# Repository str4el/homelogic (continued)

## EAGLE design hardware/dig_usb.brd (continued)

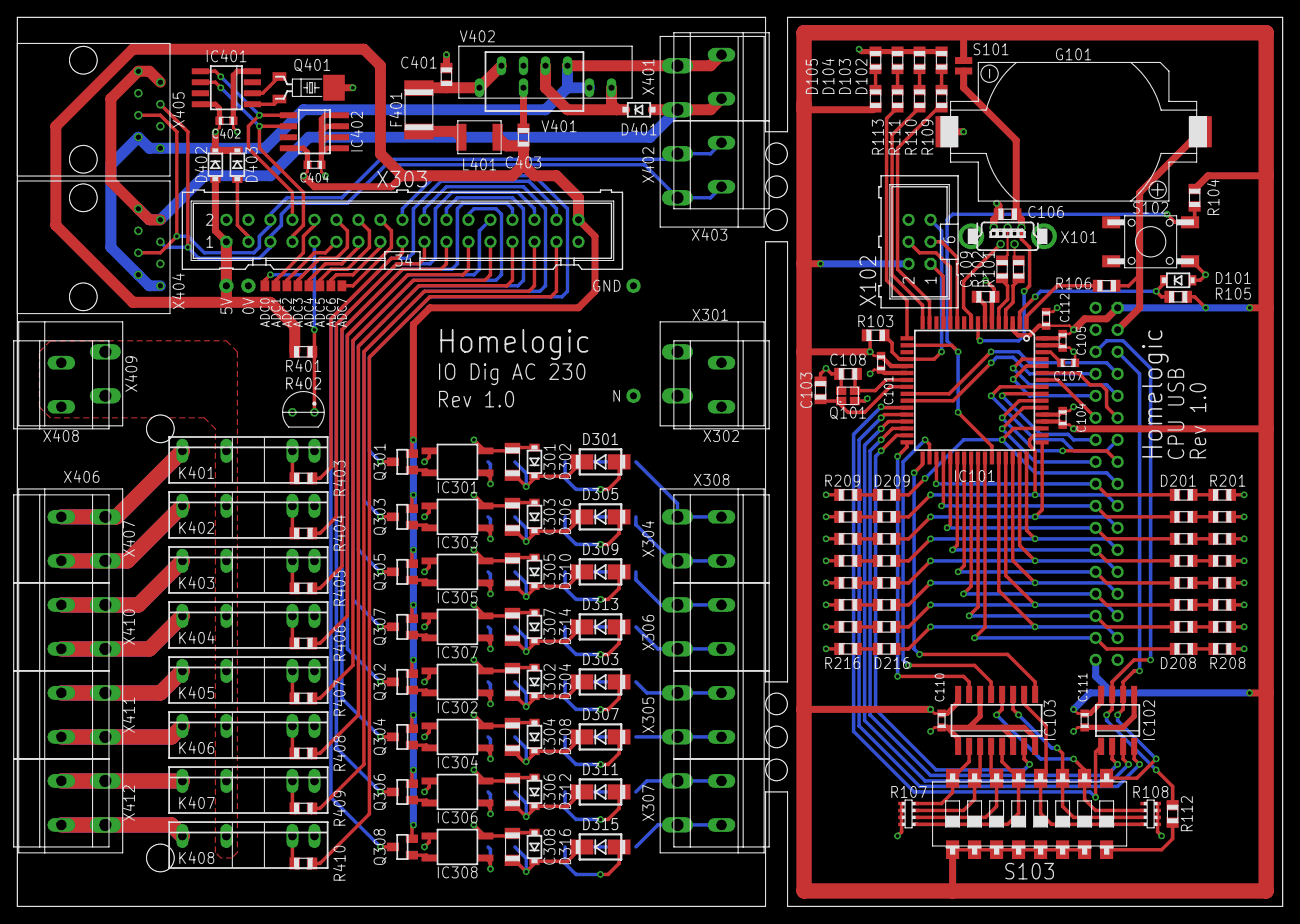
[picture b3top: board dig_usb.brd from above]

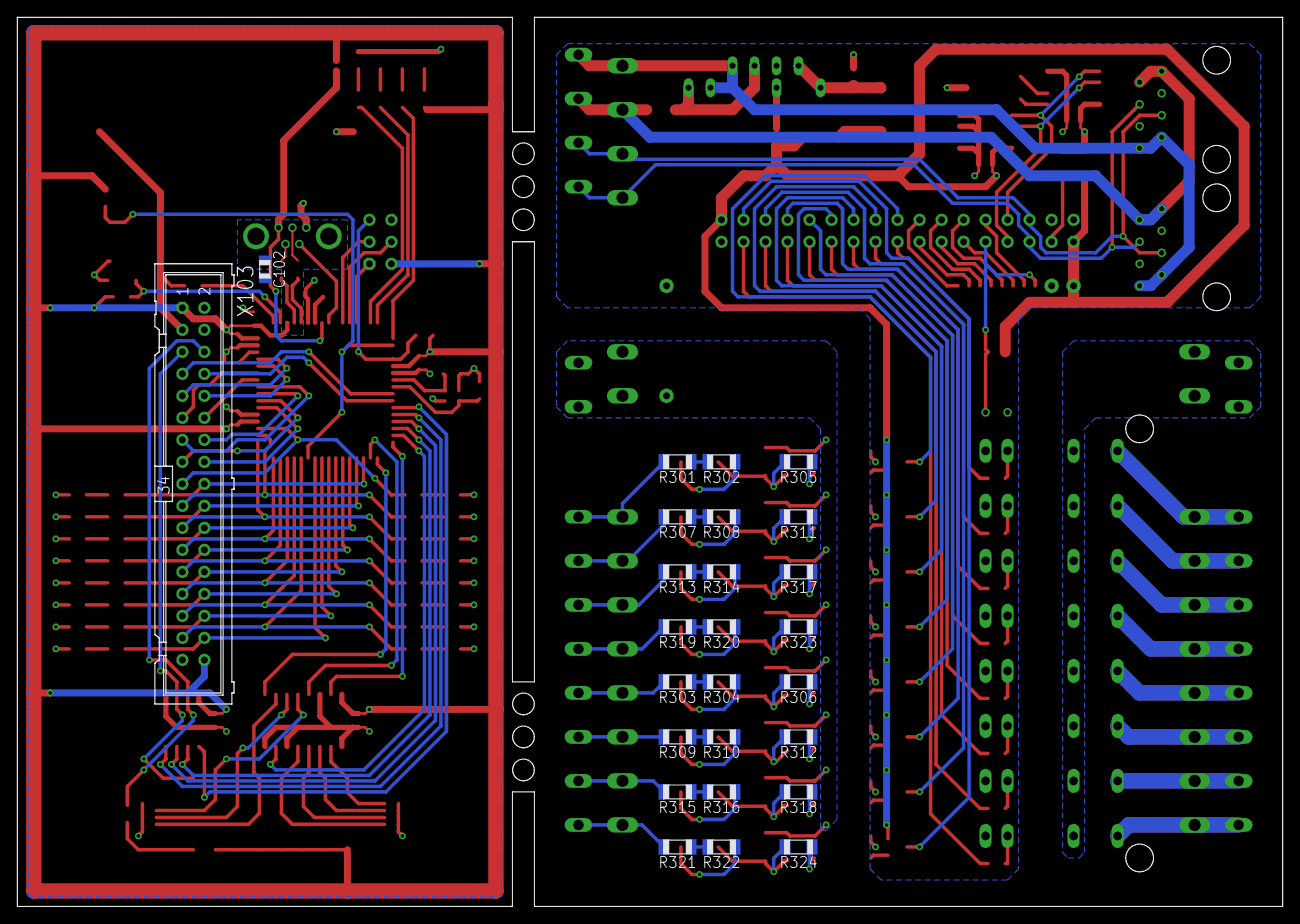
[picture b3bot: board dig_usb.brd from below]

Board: 2 copper layers, 146.1 x 102.6 mm, 201 parts (26 on the bottom side), 191 nets.

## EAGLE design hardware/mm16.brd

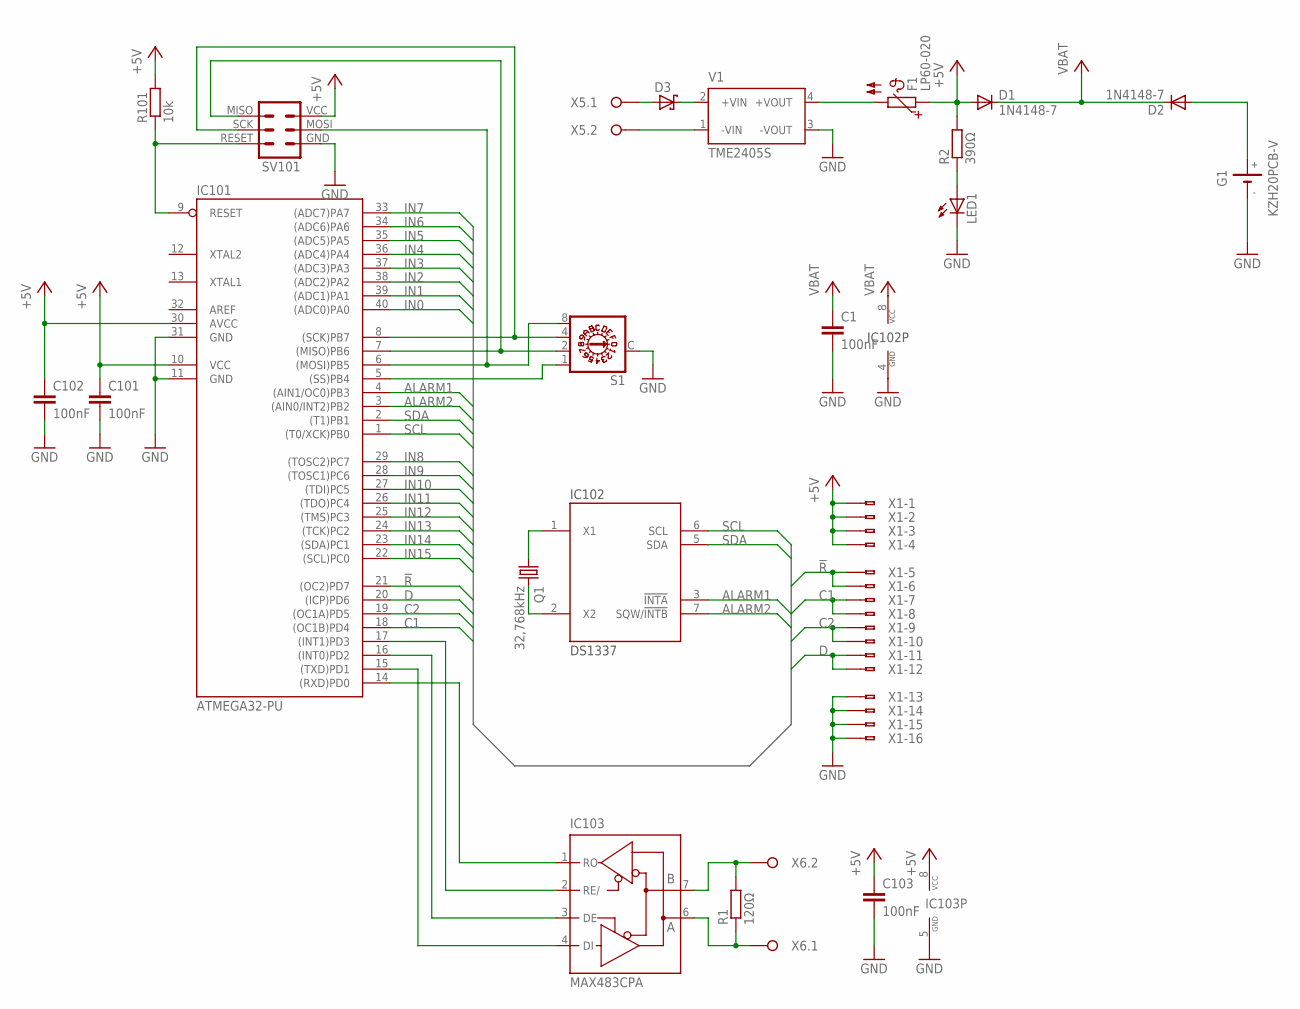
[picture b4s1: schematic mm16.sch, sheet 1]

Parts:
C1, C101, C102, C103: 100nF; C025-025X050
D1, D2: 1N4148-7; DO35-7@1
D3: SCHOTTKY-DIODEDO35-7; DO35-7
F1: LP60-020
G1: KZH20PCB-V
IC101: ATMEGA32-PU; DIL40
IC102: DS1337; DIL08
IC103: MAX483CPA; DIL08
LED1: LED3MM
Q1: 32,768kHz; TC38H
R1: 120Ω; 0204V
R2: 390Ω; 0204V
R101: 10k; 0204V
S1: P103
SV101: AVR_ISP6; ML6
V1: TME2405S; TME-24V; MPN TME 2405S
X1: WS16V
X5, X6: WAGO_236-402

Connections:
!R: IC101.21 ((OC2)PD7), X1.5, X1.6
+5V: C101.1, C102.1, C103.1, D1.A, F1.P$1 (1), IC101.10 (VCC), IC101.30 (AVCC), IC103.8 (VCC), R2.2, R101.2, SV101.VCC, X1.1, X1.2, X1.3, X1.4
ALARM1: IC101.4 ((AIN1/OC0)PB3), IC102.3 (!INTA)
ALARM2: IC101.3 ((AIN0/INT2)PB2), IC102.7 (SQW/!INTB)
C1: IC101.18 ((OC1B)PD4), X1.7, X1.8
C2: IC101.19 ((OC1A)PD5), X1.9, X1.10
D: IC101.20 ((ICP)PD6), X1.11, X1.12
GND: C1.2, C101.2, C102.2, C103.2, G1.-, IC101.11 (GND), IC101.31 (GND), IC102.4 (GND), IC103.5 (GND), LED1.K (C), S1.C, SV101.GND, V1.3 (-VOUT), X1.13, X1.14, X1.15, X1.16; also elsewhere on the board
IN0: IC101.40 ((ADC0)PA0); also elsewhere on the board
IN1: IC101.39 ((ADC1)PA1); also elsewhere on the board
IN2: IC101.38 ((ADC2)PA2); also elsewhere on the board
IN3: IC101.37 ((ADC3)PA3); also elsewhere on the board
IN4: IC101.36 ((ADC4)PA4); also elsewhere on the board
IN5: IC101.35 ((ADC5)PA5); also elsewhere on the board
IN6: IC101.34 ((ADC6)PA6); also elsewhere on the board
IN7: IC101.33 ((ADC7)PA7); also elsewhere on the board
IN8: IC101.29 ((TOSC2)PC7); also elsewhere on the board
IN9: IC101.28 ((TOSC1)PC6); also elsewhere on the board
IN10: IC101.27 ((TDI)PC5); also elsewhere on the board
IN11: IC101.26 ((TDO)PC4); also elsewhere on the board
IN12: IC101.25 ((TMS)PC3); also elsewhere on the board
IN13: IC101.24 ((TCK)PC2); also elsewhere on the board
IN14: IC101.23 ((SDA)PC1); also elsewhere on the board
IN15: IC101.22 ((SCL)PC0); also elsewhere on the board
unnamed: V1.1 (-VIN), X5.A2, X5.B2
unnamed: IC103.6 (A), R1.1, X6.A1, X6.B1
unnamed: D2.A, G1.+1 (+), G1.+2 (+)
unnamed: IC103.7 (B), R1.2, X6.A2, X6.B2
unnamed: D3.C, V1.2 (+VIN)
unnamed: D3.A, X5.A1, X5.B1
unnamed: F1.P$2 (2), V1.4 (+VOUT)
unnamed: IC101.9 (RESET), R101.1, SV101.RESET
unnamed: LED1.A, R2.1
unnamed: IC101.15 ((TXD)PD1), IC103.4 (DI)
unnamed: IC101.14 ((RXD)PD0), IC103.1 (RO)
unnamed: IC101.17 ((INT1)PD3), IC103.2 (RE/)
unnamed: IC101.16 ((INT0)PD2), IC103.3 (DE)
unnamed: IC101.6 ((MOSI)PB5), S1.8, SV101.MOSI
unnamed: IC101.7 ((MISO)PB6), S1.2, SV101.MISO
unnamed: IC101.8 ((SCK)PB7), S1.4, SV101.SCK
unnamed: IC102.1 (X1), Q1.1
unnamed: IC102.2 (X2), Q1.2
unnamed: IC101.5 ((SS)PB4), S1.1
SCL: IC101.1 ((T0/XCK)PB0), IC102.6 (SCL)
SDA: IC101.2 ((T1)PB1), IC102.5 (SDA)
VCC: C1.1, D1.C, D2.C, IC102.8 (VCC)

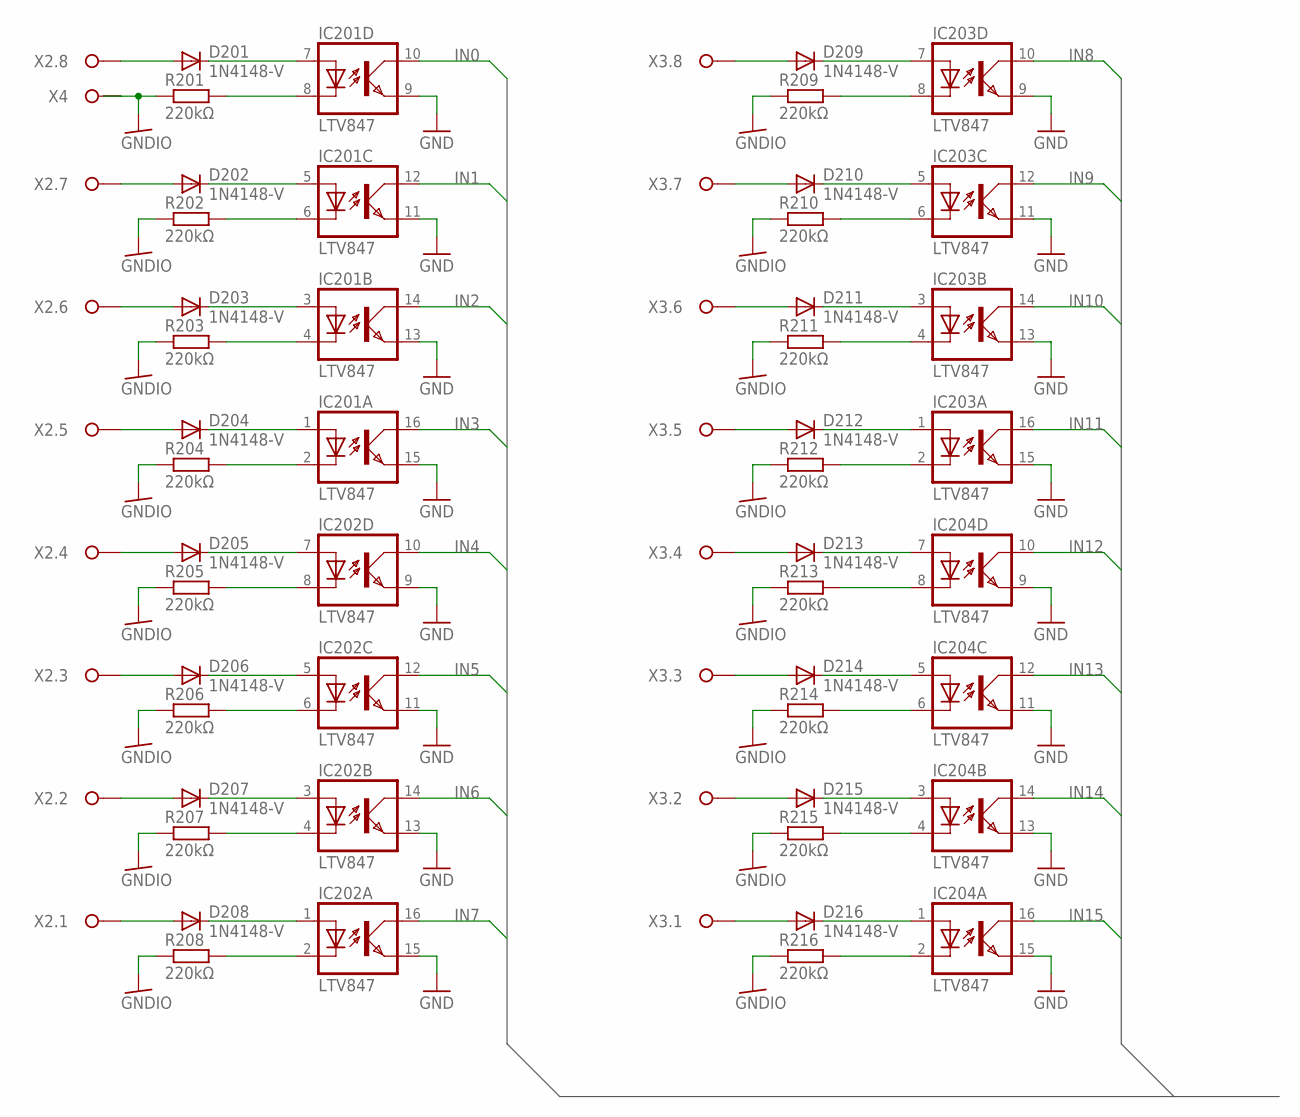
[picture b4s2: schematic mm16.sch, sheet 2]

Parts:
D201, D202, D203, D204, D205, D206, D207, D208, D209, D210, D211, D212, D213, D214, D215, D216: 1N4148-V; DO35-V
IC201, IC202, IC203, IC204: LTV847; DIL16
R201, R202, R203, R204, R205, R206, R207, R208, R209, R210, R211, R212, R213, R214, R215, R216: 220kΩ; 0204V
X2, X3: WAGO_236-408
X4: WAGO_236-401

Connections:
GND: IC201.9 (EMIT), IC201.11 (EMIT), IC201.13 (EMIT), IC201.15 (EMIT), IC202.9 (EMIT), IC202.11 (EMIT), IC202.13 (EMIT), IC202.15 (EMIT), IC203.9 (EMIT), IC203.11 (EMIT), IC203.13 (EMIT), IC203.15 (EMIT), IC204.9 (EMIT), IC204.11 (EMIT), IC204.13 (EMIT), IC204.15 (EMIT); also elsewhere on the board
GNDIO: R201.1, R202.1, R203.1, R204.1, R205.1, R206.1, R207.1, R208.1, R209.1, R210.1, R211.1, R212.1, R213.1, R214.1, R215.1, R216.1, X4.A1 (A), X4.B1 (B)
IN0: IC201.10 (COL); also elsewhere on the board
IN1: IC201.12 (COL); also elsewhere on the board
IN2: IC201.14 (COL); also elsewhere on the board
IN3: IC201.16 (COL); also elsewhere on the board
IN4: IC202.10 (COL); also elsewhere on the board
IN5: IC202.12 (COL); also elsewhere on the board
IN6: IC202.14 (COL); also elsewhere on the board
IN7: IC202.16 (COL); also elsewhere on the board
IN8: IC203.10 (COL); also elsewhere on the board
IN9: IC203.12 (COL); also elsewhere on the board
IN10: IC203.14 (COL); also elsewhere on the board
IN11: IC203.16 (COL); also elsewhere on the board
IN12: IC204.10 (COL); also elsewhere on the board
IN13: IC204.12 (COL); also elsewhere on the board
IN14: IC204.14 (COL); also elsewhere on the board
IN15: IC204.16 (COL); also elsewhere on the board
unnamed: D201.2 (C), IC201.7 (A)
unnamed: IC201.8 (C), R201.2
unnamed: D202.2 (C), IC201.5 (A)
unnamed: IC201.6 (C), R202.2
unnamed: D203.2 (C), IC201.3 (A)
unnamed: IC201.4 (C), R203.2
unnamed: D204.2 (C), IC201.1 (A)
unnamed: IC201.2 (C), R204.2
unnamed: D205.2 (C), IC202.7 (A)
unnamed: IC202.8 (C), R205.2
unnamed: D206.2 (C), IC202.5 (A)
unnamed: IC202.6 (C), R206.2
unnamed: D207.2 (C), IC202.3 (A)
unnamed: IC202.4 (C), R207.2
unnamed: D208.2 (C), IC202.1 (A)
unnamed: IC202.2 (C), R208.2
unnamed: D209.2 (C), IC203.7 (A)
unnamed: IC203.8 (C), R209.2
unnamed: D210.2 (C), IC203.5 (A)
unnamed: IC203.6 (C), R210.2
unnamed: D211.2 (C), IC203.3 (A)
unnamed: IC203.4 (C), R211.2
unnamed: D212.2 (C), IC203.1 (A)
unnamed: IC203.2 (C), R212.2
unnamed: D213.2 (C), IC204.7 (A)
unnamed: IC204.8 (C), R213.2
unnamed: D214.2 (C), IC204.5 (A)
unnamed: IC204.6 (C), R214.2
unnamed: D215.2 (C), IC204.3 (A)
unnamed: IC204.4 (C), R215.2
unnamed: D216.2 (C), IC204.1 (A)
unnamed: IC204.2 (C), R216.2
unnamed: D204.1 (A), X2.A5, X2.B5
unnamed: D203.1 (A), X2.A6, X2.B6
unnamed: D202.1 (A), X2.A7, X2.B7
unnamed: D201.1 (A), X2.A8, X2.B8
unnamed: D205.1 (A), X2.A4, X2.B4
unnamed: D206.1 (A), X2.A3, X2.B3
unnamed: D207.1 (A), X2.A2, X2.B2
unnamed: D208.1 (A), X2.A1, X2.B1
unnamed: D216.1 (A), X3.A1, X3.B1
unnamed: D215.1 (A), X3.A2, X3.B2
unnamed: D214.1 (A), X3.A3, X3.B3
unnamed: D213.1 (A), X3.A4, X3.B4
unnamed: D212.1 (A), X3.A5, X3.B5
unnamed: D211.1 (A), X3.A6, X3.B6
unnamed: D209.1 (A), X3.A8, X3.B8
unnamed: D210.1 (A), X3.A7, X3.B7

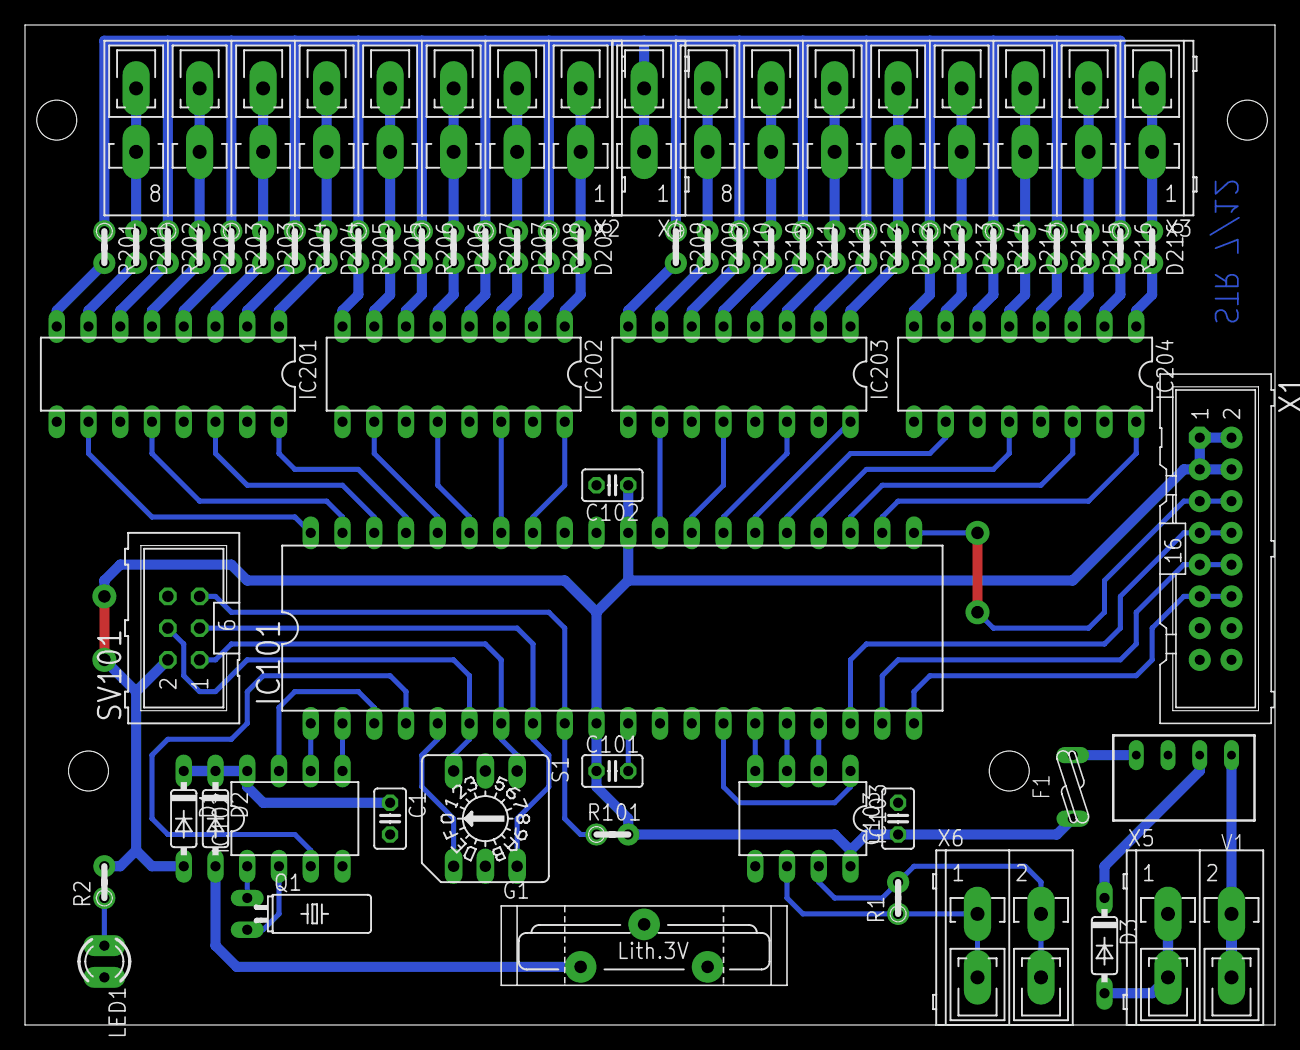
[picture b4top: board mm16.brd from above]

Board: 2 copper layers, 100.0 x 80.0 mm, 62 parts (0 on the bottom side), 95 nets.

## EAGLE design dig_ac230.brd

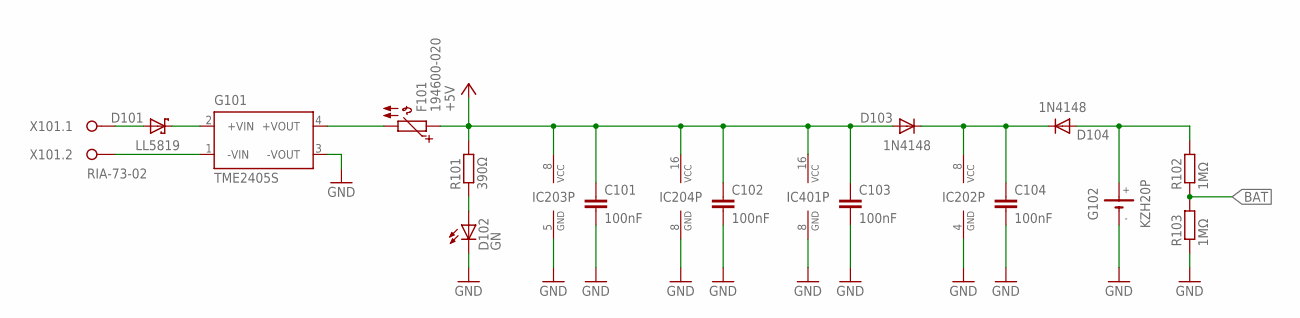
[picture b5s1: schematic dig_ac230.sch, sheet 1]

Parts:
C101, C102, C103, C104: 100nF; CHIP_0805
D101: LL5819; MELF
D102: GN; LED3MM
D103, D104: 1N4148; MINIMELF
F101: 194600-020; CHIP_1812
G101: TME2405S; TME-24V; MPN TME 2405S
G102: KZH20P
IC202: DS1337S; SOP08_127
IC203: MAX487CSA; SOP08_127
IC204: 74HC166D; SOP16_127
IC401: 74HC595D; SOP16_127
R101: 390Ω; CHIP_0805
R102, R103: 1MΩ; CHIP_0805
X101: RIA-73-02

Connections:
+5V: C101.1, C102.1, C103.1, D103.A, F101.1, IC203.8 (VCC), IC204.16 (VCC), IC401.16 (VCC), R101.2; also elsewhere on the board
BAT: R102.1, R103.2; also elsewhere on the board
GND: C101.2, C102.2, C103.2, C104.2, D102.K (C), G101.3 (-VOUT), G102.N (-), IC202.4 (GND), IC203.5 (GND), IC204.8 (GND), IC401.8 (GND), R103.1; also elsewhere on the board
unnamed: G101.1 (-VIN), X101.2
unnamed: D104.A, G102.P1 (+), G102.P2 (+), R102.2
unnamed: D101.K, G101.2 (+VIN)
unnamed: D101.A, X101.1
unnamed: F101.2, G101.4 (+VOUT)
unnamed: D102.A, R101.1
unnamed: C104.1, D103.K, D104.K, IC202.8 (VCC)

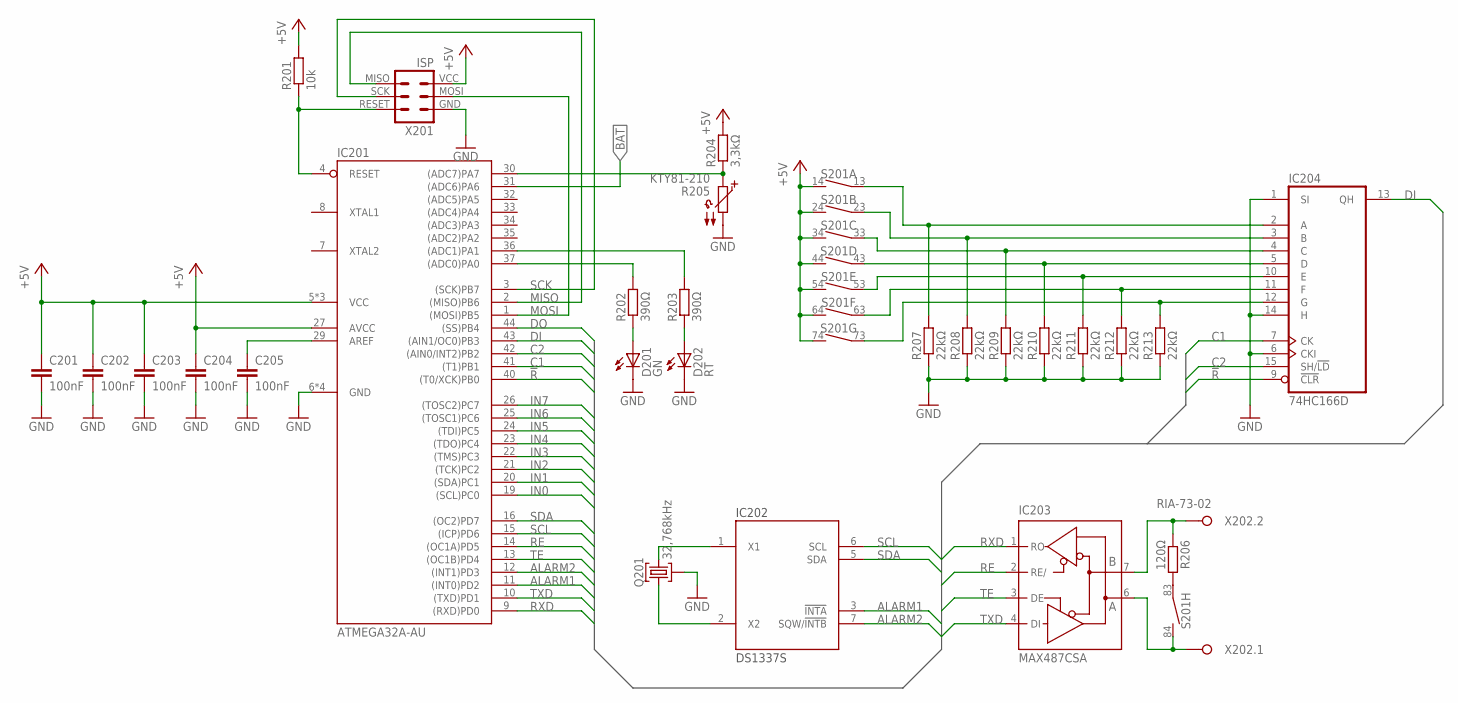
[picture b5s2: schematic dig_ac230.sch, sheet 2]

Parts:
C201, C202, C203, C204, C205: 100nF; CHIP_0805
D201: GN; LED3MM
D202: RT; LED3MM
IC201: ATMEGA32A-AU; QFP44_08
IC202: DS1337S; SOP08_127
IC203: MAX487CSA; SOP08_127
IC204: 74HC166D; SOP16_127
Q201: 32,768kHz; MS1V-T1K
R201: 10k; CHIP_0805
R202, R203: 390Ω; CHIP_0805
R204: 3,3kΩ; CHIP_0805
R205: KTY81-210; TO92
R206: 120Ω; CHIP_0805
R207, R208, R209, R210, R211, R212, R213: 22kΩ; CHIP_0805
S201: DP08
X201: ISP; ML6L
X202: RIA-73-02

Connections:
!R: IC201.40 ((T0/XCK)PB0), IC204.9 (!CLR); also elsewhere on the board
+5V: C201.1, C202.1, C203.1, C204.1, IC201.5 (VCC), IC201.17 (VCC), IC201.27 (AVCC), IC201.38 (VCC), R201.2, R204.2, S201.14 (4), S201.24 (4), S201.34 (4), S201.44 (4), S201.54 (4), S201.64 (4), S201.74 (4), X201.VCC; also elsewhere on the board
ALARM1: IC201.11 ((INT0)PD2), IC202.3 (!INTA)
ALARM2: IC201.12 ((INT1)PD3), IC202.7 (SQW/!INTB)
BAT: IC201.31 ((ADC6)PA6); also elsewhere on the board
C1: IC201.41 ((T1)PB1), IC204.7 (CK); also elsewhere on the board
C2: IC201.42 ((AIN0/INT2)PB2), IC204.15 (SH/!LD); also elsewhere on the board
DI: IC201.43 ((AIN1/OC0)PB3), IC204.13 (QH)
DO: IC201.44 ((SS)PB4); also elsewhere on the board
GND: C201.2, C202.2, C203.2, C204.2, C205.2, D201.K (C), D202.K (C), IC201.6 (GND), IC201.18 (GND), IC201.28 (GND), IC201.39 (GND), IC204.1 (SI), IC204.6 (CKI), IC204.14 (H), Q201.G, R205.2, R207.1, R208.1, R209.1, R210.1, R211.1, R212.1, R213.1, X201.GND; also elsewhere on the board
IN0: IC201.19 ((SCL)PC0); also elsewhere on the board
IN1: IC201.20 ((SDA)PC1); also elsewhere on the board
IN2: IC201.21 ((TCK)PC2); also elsewhere on the board
IN3: IC201.22 ((TMS)PC3); also elsewhere on the board
IN4: IC201.23 ((TDO)PC4); also elsewhere on the board
IN5: IC201.24 ((TDI)PC5); also elsewhere on the board
IN6: IC201.25 ((TOSC1)PC6); also elsewhere on the board
IN7: IC201.26 ((TOSC2)PC7); also elsewhere on the board
MISO: IC201.2 ((MISO)PB6), X201.MISO
MOSI: IC201.1 ((MOSI)PB5), X201.MOSI
unnamed: IC203.6 (A), S201.84 (4), X202.1
unnamed: IC203.7 (B), R206.1, X202.2
unnamed: C205.1, IC201.29 (AREF)
unnamed: IC204.2 (A), R207.2, S201.13 (3)
unnamed: IC204.3 (B), R208.2, S201.23 (3)
unnamed: IC204.4 (C), R209.2, S201.33 (3)
unnamed: IC204.5 (D), R210.2, S201.43 (3)
unnamed: IC204.10 (E), R211.2, S201.53 (3)
unnamed: IC204.11 (F), R212.2, S201.63 (3)
unnamed: IC204.12 (G), R213.2, S201.73 (3)
unnamed: R206.2, S201.83 (3)
unnamed: IC201.4 (RESET), R201.1, X201.RESET
unnamed: IC201.30 ((ADC7)PA7), R204.1, R205.1
unnamed: D201.A, R202.1
unnamed: D202.A, R203.1
unnamed: IC201.37 ((ADC0)PA0), R202.2
unnamed: IC201.36 ((ADC1)PA1), R203.2
unnamed: IC202.1 (X1), Q201.2
unnamed: IC202.2 (X2), Q201.1
RE: IC201.14 ((OC1A)PD5), IC203.2 (RE/)
RXD: IC201.9 ((RXD)PD0), IC203.1 (RO)
SCK: IC201.3 ((SCK)PB7), X201.SCK
SCL: IC201.15 ((ICP)PD6), IC202.6 (SCL)
SDA: IC201.16 ((OC2)PD7), IC202.5 (SDA)
TE: IC201.13 ((OC1B)PD4), IC203.3 (DE)
TXD: IC201.10 ((TXD)PD1), IC203.4 (DI)

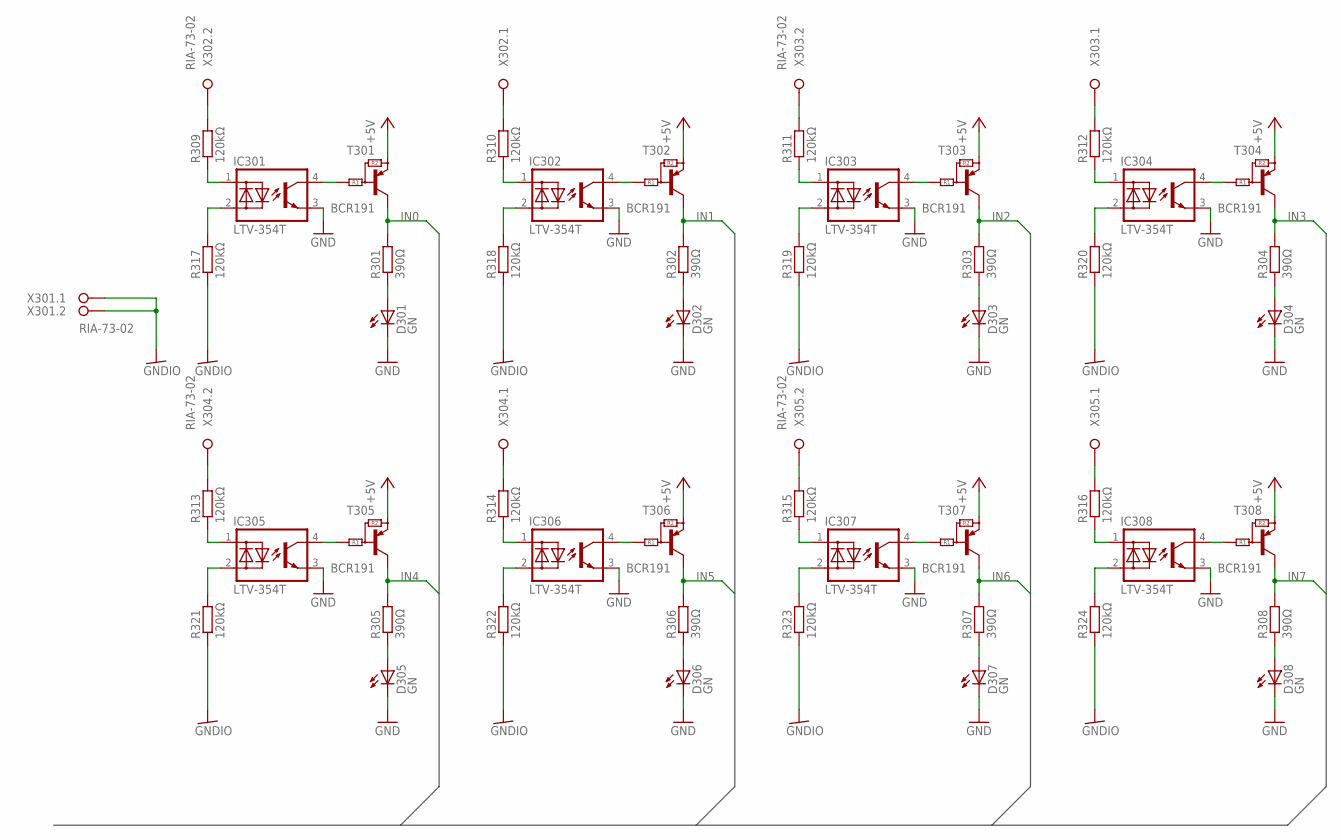
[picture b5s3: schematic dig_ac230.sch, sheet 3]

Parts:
D301, D302, D303, D304, D305, D306, D307, D308: GN; LED3MM
IC301, IC302, IC303, IC304, IC305, IC306, IC307, IC308: LTV-354T; SOP04_254
R301, R302, R303, R304, R305, R306, R307, R308: 390Ω; CHIP_0805
R309, R310, R311, R312, R313, R314, R315, R316, R317, R318, R319, R320, R321, R322, R323, R324: 120kΩ; CHIP_1206
T301, T302, T303, T304, T305, T306, T307, T308: BCR191; SOT23
X301, X302, X303, X304, X305: RIA-73-02

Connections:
+5V: T301.2 (E), T302.2 (E), T303.2 (E), T304.2 (E), T305.2 (E), T306.2 (E), T307.2 (E), T308.2 (E); also elsewhere on the board
GND: D301.K (C), D302.K (C), D303.K (C), D304.K (C), D305.K (C), D306.K (C), D307.K (C), D308.K (C), IC301.3 (E), IC302.3 (E), IC303.3 (E), IC304.3 (E), IC305.3 (E), IC306.3 (E), IC307.3 (E), IC308.3 (E); also elsewhere on the board
GNDIO: R317.1, R318.1, R319.1, R320.1, R321.1, R322.1, R323.1, R324.1, X301.1, X301.2
IN0: R301.2, T301.3 (C); also elsewhere on the board
IN1: R302.2, T302.3 (C); also elsewhere on the board
IN2: R303.2, T303.3 (C); also elsewhere on the board
IN3: R304.2, T304.3 (C); also elsewhere on the board
IN4: R305.2, T305.3 (C); also elsewhere on the board
IN5: R306.2, T306.3 (C); also elsewhere on the board
IN6: R307.2, T307.3 (C); also elsewhere on the board
IN7: R308.2, T308.3 (C); also elsewhere on the board
unnamed: R309.2, X302.2
unnamed: IC301.1 (A), R309.1
unnamed: IC301.2 (K), R317.2
unnamed: R310.2, X302.1
unnamed: IC302.1 (A), R310.1
unnamed: IC302.2 (K), R318.2
unnamed: R311.2, X303.2
unnamed: IC303.1 (A), R311.1
unnamed: IC303.2 (K), R319.2
unnamed: R312.2, X303.1
unnamed: IC304.1 (A), R312.1
unnamed: IC304.2 (K), R320.2
unnamed: R313.2, X304.2
unnamed: IC305.1 (A), R313.1
unnamed: IC305.2 (K), R321.2
unnamed: R314.2, X304.1
unnamed: D304.A, R304.1
unnamed: IC306.1 (A), R314.1
unnamed: D303.A, R303.1
unnamed: IC306.2 (K), R322.2
unnamed: D302.A, R302.1
unnamed: IC307.1 (A), R315.1
unnamed: D301.A, R301.1
unnamed: IC307.2 (K), R323.2
unnamed: IC304.4 (C), T304.1 (B)
unnamed: D305.A, R305.1
unnamed: R315.2, X305.2
unnamed: D306.A, R306.1
unnamed: R316.2, X305.1
unnamed: D307.A, R307.1
unnamed: IC303.4 (C), T303.1 (B)
unnamed: IC308.1 (A), R316.1
unnamed: IC302.4 (C), T302.1 (B)
unnamed: IC301.4 (C), T301.1 (B)
unnamed: D308.A, R308.1
unnamed: IC308.2 (K), R324.2
unnamed: IC305.4 (C), T305.1 (B)
unnamed: IC306.4 (C), T306.1 (B)
unnamed: IC307.4 (C), T307.1 (B)
unnamed: IC308.4 (C), T308.1 (B)

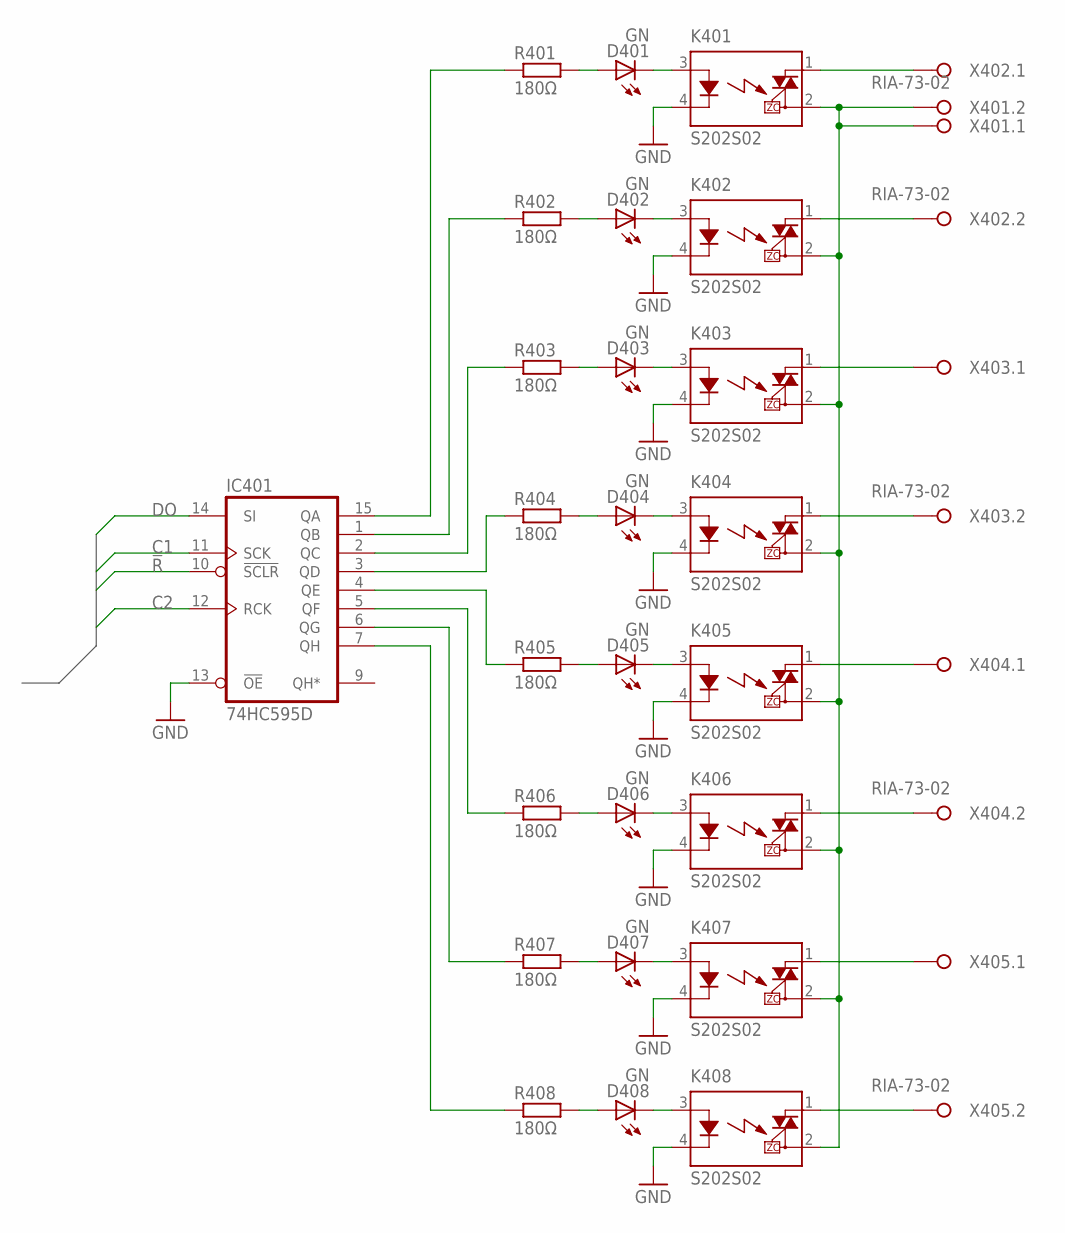
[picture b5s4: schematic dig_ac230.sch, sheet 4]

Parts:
D401, D402, D403, D404, D405, D406, D407, D408: GN; LED3MM
IC401: 74HC595D; SOP16_127
K401, K402, K403, K404, K405, K406, K407, K408: S202S02; SIP4
R401, R402, R403, R404, R405, R406, R407, R408: 180Ω; CHIP_0805
X401, X402, X403, X404, X405: RIA-73-02

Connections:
!R: IC401.10 (!SCLR); also elsewhere on the board
C1: IC401.11 (SCK); also elsewhere on the board
C2: IC401.12 (RCK); also elsewhere on the board
DO: IC401.14 (SI); also elsewhere on the board
GND: IC401.13 (!OE), K401.4 (K), K402.4 (K), K403.4 (K), K404.4 (K), K405.4 (K), K406.4 (K), K407.4 (K), K408.4 (K); also elsewhere on the board
L: K401.2 (DS2), K402.2 (DS2), K403.2 (DS2), K404.2 (DS2), K405.2 (DS2), K406.2 (DS2), K407.2 (DS2), K408.2 (DS2), X401.1, X401.2
unnamed: D401.K (C), K401.3 (A)
unnamed: D402.K (C), K402.3 (A)
unnamed: D403.K (C), K403.3 (A)
unnamed: D404.K (C), K404.3 (A)
unnamed: D405.K (C), K405.3 (A)
unnamed: D406.K (C), K406.3 (A)
unnamed: D407.K (C), K407.3 (A)
unnamed: D408.K (C), K408.3 (A)
unnamed: IC401.15 (QA), R401.1
unnamed: IC401.1 (QB), R402.1
unnamed: IC401.2 (QC), R403.1
unnamed: IC401.3 (QD), R404.1
unnamed: IC401.4 (QE), R405.1
unnamed: IC401.5 (QF), R406.1
unnamed: IC401.6 (QG), R407.1
unnamed: IC401.7 (QH), R408.1
unnamed: K401.1 (DS1), X402.1
unnamed: K402.1 (DS1), X402.2
unnamed: K403.1 (DS1), X403.1
unnamed: K404.1 (DS1), X403.2
unnamed: K405.1 (DS1), X404.1
unnamed: K406.1 (DS1), X404.2
unnamed: K407.1 (DS1), X405.1
unnamed: K408.1 (DS1), X405.2
unnamed: D401.A, R401.2
unnamed: D402.A, R402.2
unnamed: D403.A, R403.2
unnamed: D404.A, R404.2
unnamed: D405.A, R405.2
unnamed: D406.A, R406.2
unnamed: D407.A, R407.2
unnamed: D408.A, R408.2

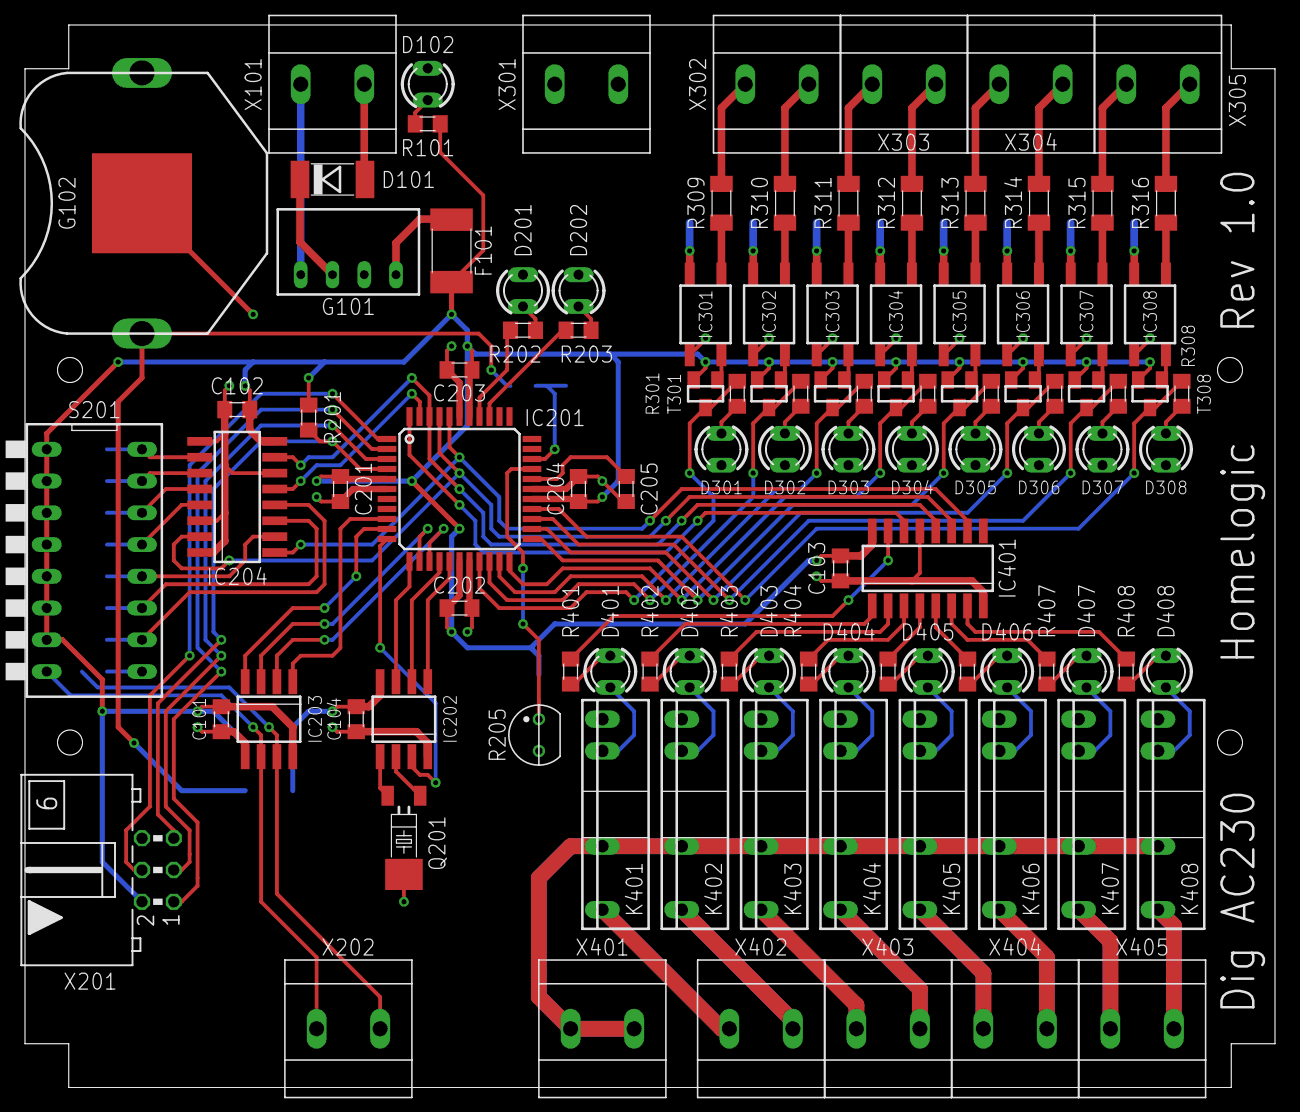
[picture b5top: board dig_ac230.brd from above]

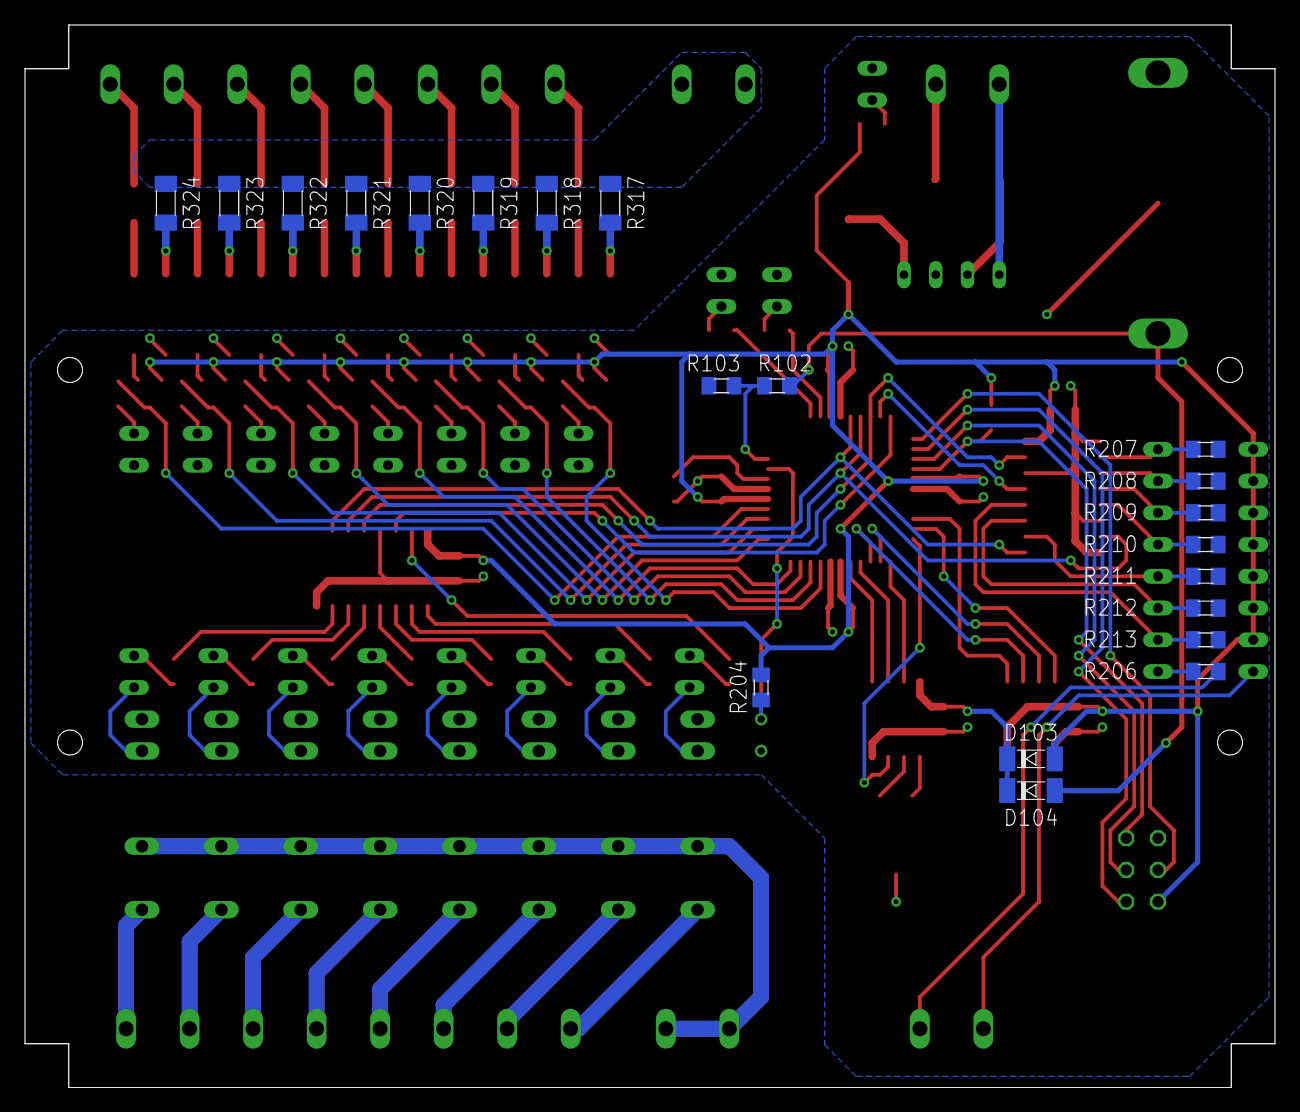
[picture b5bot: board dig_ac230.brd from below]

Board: 2 copper layers, 100.0 x 85.0 mm, 126 parts (21 on the bottom side), 127 nets.
